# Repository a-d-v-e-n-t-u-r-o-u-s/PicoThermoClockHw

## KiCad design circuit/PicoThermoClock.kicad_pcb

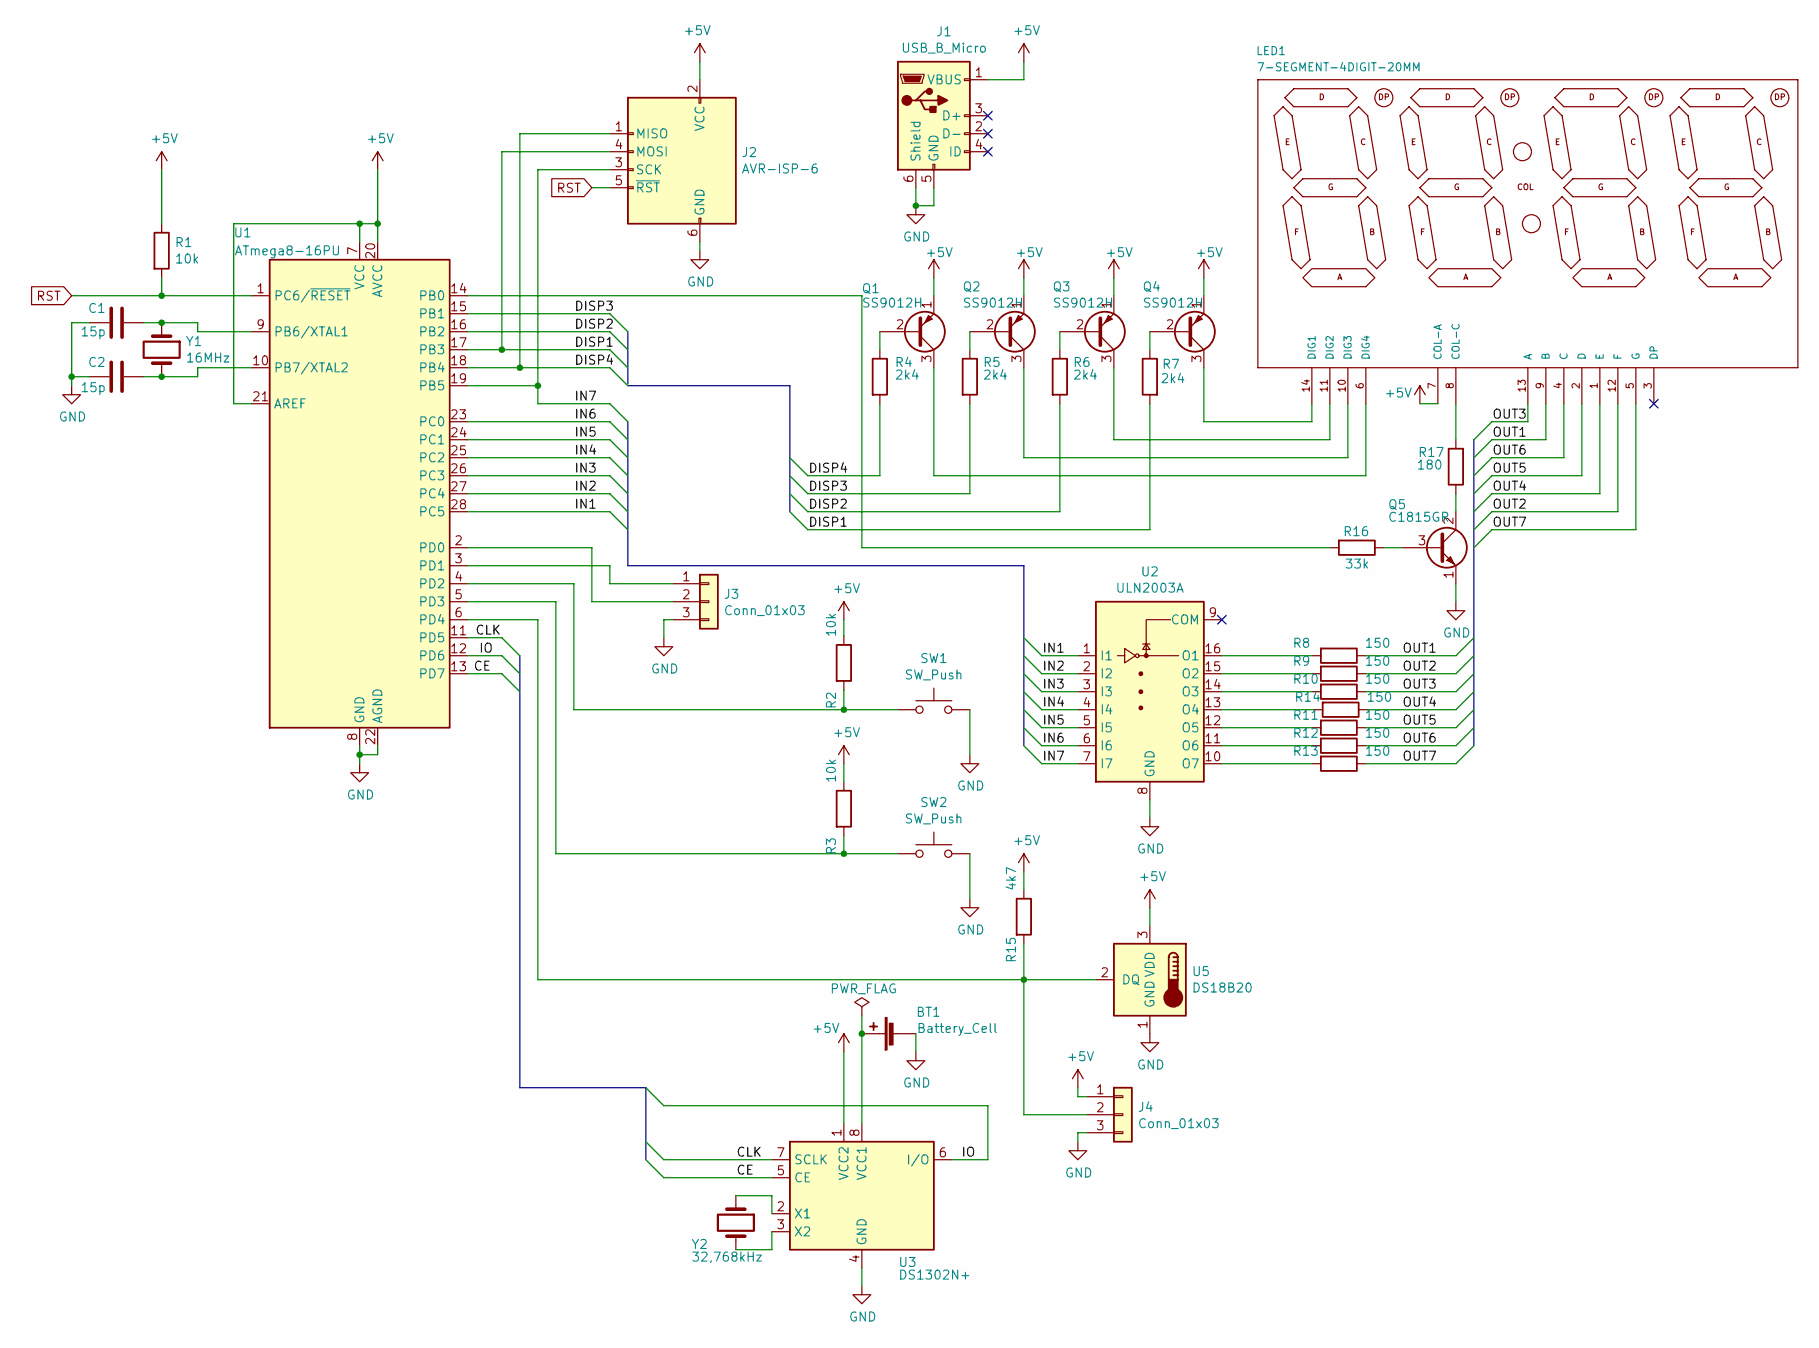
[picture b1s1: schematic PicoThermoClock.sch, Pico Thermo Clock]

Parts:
BT1: Battery_Cell; BATTCOM_20MM_PTH
C1, C2: 15p; C_Disc_D3.4mm_W2.1mm_P2.50mm
J1: USB_B_Micro; USB_Micro-B_Molex-105017-0001
J2: AVR-ISP-6; PinSocket_2x03_P2.54mm_Vertical
J3: Conn_01x03; PinHeader_1x03_P2.54mm_Vertical
J4: Conn_01x03; PinHeader_1x03_P2.54mm_Horizontal
LED1: 7-SEGMENT-4DIGIT-20MM
Q1, Q2, Q3, Q4: SS9012H; TO-92_Inline
Q5: C1815GR; TO-92_Inline
R1, R2, R3: 10k; R_Axial_DIN0207_L6.3mm_D2.5mm_P10.16mm_Horizontal
R4, R5, R6, R7: 2k4; R_Axial_DIN0207_L6.3mm_D2.5mm_P10.16mm_Horizontal
R8, R9, R10, R11, R12, R13, R14: 150; R_Axial_DIN0207_L6.3mm_D2.5mm_P10.16mm_Horizontal
R15: 4k7; R_Axial_DIN0207_L6.3mm_D2.5mm_P10.16mm_Horizontal
R16: 33k; R_Axial_DIN0207_L6.3mm_D2.5mm_P10.16mm_Horizontal
R17: 180; R_Axial_DIN0207_L6.3mm_D2.5mm_P10.16mm_Horizontal
SW1, SW2: SW_Push; SW_PUSH_6mm_H4.3mm
U1: ATmega8-16PU; DIP-28_W7.62mm_Socket_LongPads
U2: ULN2003A; DIP-16_W7.62mm_Socket_LongPads
U3: DS1302N+; DIP-8_W7.62mm
U5: DS18B20; TO-92_Inline
Y1: 16MHz; Crystal_HC49-4H_Vertical
Y2: 32,768kHz; Crystal_C38-LF_D3.0mm_L8.0mm_Vertical

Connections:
+5V: J1.1 (VBUS), J2.2 (VCC), J4.1, LED1.7 (COL-A), Q1.1 (E), Q2.1 (E), Q3.1 (E), Q4.1 (E), R1.1, R2.1, R3.1, R15.1, U1.7 (VCC), U1.20 (AVCC), U1.21 (AREF), U3.1 (VCC2), U5.3 (VDD)
/CE: U1.13 (PD7), U3.5 (CE)
/CLK: U1.11 (PD5), U3.7 (SCLK)
/DISP1: J2.4 (MOSI), R7.2, U1.17 (PB3)
/DISP2: R6.2, U1.16 (PB2)
/DISP3: R5.2, U1.15 (PB1)
/DISP4: J2.1 (MISO), R4.2, U1.18 (PB4)
/IN1: U1.28 (PC5), U2.1 (I1)
/IN2: U1.27 (PC4), U2.2 (I2)
/IN3: U1.26 (PC3), U2.3 (I3)
/IN4: U1.25 (PC2), U2.4 (I4)
/IN5: U1.24 (PC1), U2.5 (I5)
/IN6: U1.23 (PC0), U2.6 (I6)
/IN7: J2.3 (SCK), U1.19 (PB5), U2.7 (I7)
/IO: U1.12 (PD6), U3.6 (I/O)
/OUT1: LED1.9 (B), R8.1
/OUT2: LED1.12 (F), R9.1
/OUT3: LED1.13 (A), R10.1
/OUT4: LED1.1 (E), R14.1
/OUT5: LED1.2 (D), R11.1
/OUT6: LED1.4 (C), R12.1
/OUT7: LED1.5 (G), R13.1
GND: BT1.2 (-), C1.2, C2.2, J1.5 (GND), J1.6 (Shield), J2.6 (GND), J3.3, J4.3, Q5.1 (E), SW1.2, SW2.2, U1.8 (GND), U1.22 (AGND), U2.8 (GND), U3.4 (GND), U5.1 (GND)
unnamed: BT1.1 (+), U3.8 (VCC1)
unnamed: C1.1, U1.9 (PB6/XTAL1), Y1.1
unnamed: C2.1, U1.10 (PB7/XTAL2), Y1.2
unnamed: J3.1, U1.3 (PD1)
unnamed: J3.2, U1.2 (PD0)
unnamed: J4.2, R15.2, U1.6 (PD4), U5.2 (DQ)
unnamed: LED1.6 (DIG4), Q1.3 (C)
unnamed: LED1.8 (COL-C), R17.2
unnamed: LED1.10 (DIG3), Q2.3 (C)
unnamed: LED1.11 (DIG2), Q3.3 (C)
unnamed: LED1.14 (DIG1), Q4.3 (C)
unnamed: Q1.2 (B), R4.1
unnamed: Q2.2 (B), R5.1
unnamed: Q3.2 (B), R6.1
unnamed: Q4.2 (B), R7.1
unnamed: Q5.2 (C), R17.1
unnamed: Q5.3 (B), R16.1
unnamed: R2.2, SW1.1, U1.4 (PD2)
unnamed: R3.2, SW2.1, U1.5 (PD3)
unnamed: R8.2, U2.16 (O1)
unnamed: R9.2, U2.15 (O2)
unnamed: R10.2, U2.14 (O3)
unnamed: R11.2, U2.12 (O5)
unnamed: R12.2, U2.11 (O6)
unnamed: R13.2, U2.10 (O7)
unnamed: R14.2, U2.13 (O4)
unnamed: R16.2, U1.14 (PB0)
unnamed: U3.2 (X1), Y2.1
unnamed: U3.3 (X2), Y2.2
RST: J2.5 (~RST), R1.2, U1.1 (PC6/~RESET)

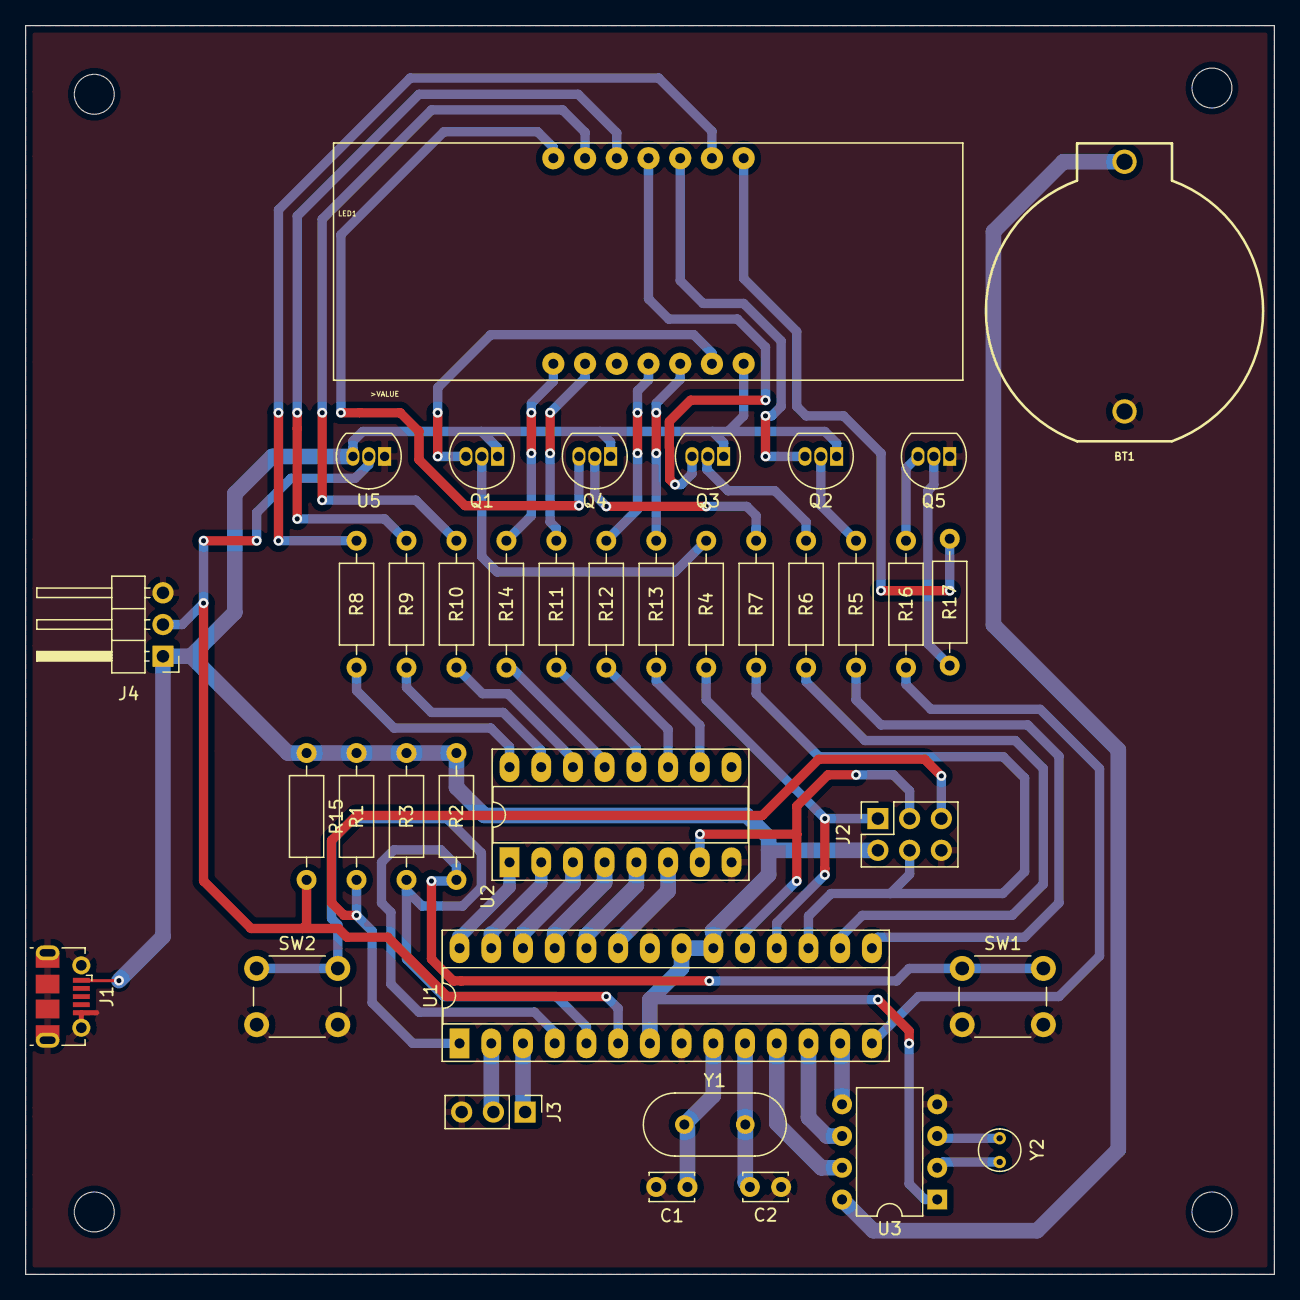
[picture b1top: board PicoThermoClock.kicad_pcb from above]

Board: 4 copper layers, 100.0 x 100.0 mm, 38 parts (0 on the bottom side), 53 nets.

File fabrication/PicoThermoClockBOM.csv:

"Id";"Designator";"Package";"Quantity";"Designation";"Supplier and ref";
1;"REF**,REF**,REF**,REF**";"MountingHole_3.2mm_M3";4;"MountingHole_3.2mm_M3";;;
2;"Y2";"Crystal_C38-LF_D3.0mm_L8.0mm_Vertical";1;"32,768kHz";;;
3;"Y1";"Crystal_HC49-4H_Vertical";1;"16MHz";;;
4;"U5";"TO-92_Inline";1;"DS18B20";;;
5;"U3";"DIP-8_W7.62mm";1;"DS1302N+";;;
6;"U2";"DIP-16_W7.62mm_Socket_LongPads";1;"ULN2003A";;;
7;"U1";"DIP-28_W7.62mm_Socket_LongPads";1;"ATmega8-16PU";;;
8;"SW2,SW1";"SW_PUSH_6mm_H4.3mm";2;"SW_Push";;;
9;"R14,R13,R12,R11,R10,R9,R8";"R_Axial_DIN0207_L6.3mm_D2.5mm_P10.16mm_Horizontal";7;"150";;;
10;"R3,R2,R1";"R_Axial_DIN0207_L6.3mm_D2.5mm_P10.16mm_Horizontal";3;"10k";;;
11;"LED1";"7-SEGMENT-4DIGIT-20MM";1;"7-SEGMENT-4DIGIT-20MM";;;
12;"J4";"PinHeader_1x03_P2.54mm_Horizontal";1;"Conn_01x03";;;
13;"J3";"PinHeader_1x03_P2.54mm_Vertical";1;"Conn_01x03";;;
14;"J2";"PinSocket_2x03_P2.54mm_Vertical";1;"AVR-ISP-6";;;
15;"J1";"USB_Micro-B_Molex-105017-0001";1;"USB_B_Micro";;;
16;"C2,C1";"C_Disc_D3.4mm_W2.1mm_P2.50mm";2;"15p";;;
17;"BT1";"BATTCOM_20MM_PTH";1;"Battery_Cell";;;
18;"R17";"R_Axial_DIN0207_L6.3mm_D2.5mm_P10.16mm_Horizontal";1;"180";;;
19;"R16";"R_Axial_DIN0207_L6.3mm_D2.5mm_P10.16mm_Horizontal";1;"33k";;;
20;"R7,R6,R5,R4";"R_Axial_DIN0207_L6.3mm_D2.5mm_P10.16mm_Horizontal";4;"2k4";;;
21;"Q5";"TO-92_Inline";1;"C1815GR";;;
22;"Q4,Q3,Q2,Q1";"TO-92_Inline";4;"SS9012H";;;

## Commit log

2020-10-05 HW: add KiCad project files
2020-10-05 HW: add gerber files and BOM list
2020-10-05 HW: remove redundant project file
2020-10-05 HW: change version to V.0.0.0
2020-10-05 HW: add .gitignore file
2020-10-06 HW: further update of the .gitignore file for KiCad project
2020-10-06 HW: add submodule for custom libs
2020-10-06 HW: add submodule with adafruit libraries
2020-10-06 HW: add sparkfun libs as submodule
2020-10-06 HW: add digikey libs as submodule
2020-10-06 HW: change SHA-1 sum of adventurous lib
2020-10-06 HW: add project specific symbol libraries
2020-10-07 HW: add further symbolic libs
2020-10-07 HW: add footprint libraries
2020-10-20 PCB: fix labels
2020-10-20 PRO: import JLCPCB rules from below github project
    https://github.com/sethhillbrand/kicad_templates
2020-10-20 PCB: fix missing GND pin connection
2020-10-20 GIT: add additional files to .gitignore
2020-11-07 Lock the mounting holes
2020-11-07 Fix missing resistor
    Add additional path widths
2020-11-07 Change revision to 0.0.1
2020-11-07 Refresh the polygons
2020-11-07 Apply changed footprint to the pcb
